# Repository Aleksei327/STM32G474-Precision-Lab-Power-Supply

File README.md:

# Precision Programmable Laboratory Power Supply

[Русская версия](README.ru.md)

A hardware development project for a galvanically isolated, fully programmable laboratory power supply. The design combines a tracking synchronous buck preregulator with a fast linear post-regulator to provide high efficiency without giving up low output noise.

> **Development status (17 November 2026): the power supply is running and working.** Both boards are assembled and powered up; the synchronous buck preregulator with its tracking loop, the linear post-regulator and the digital current limit all work under load. Verified on the bench so far: regulated output from near zero to 50 V into a resistive load, a 35-minute run at 50 V / 0.63 A with the output held within 49.998–50.001 V, and the current limit holding from 1 mA to 1.5 A. Testing and assembly are in progress: operation at several amps, short-circuit behaviour, and accuracy measurements against a reference meter are next. Until those results are published, the specification table below lists design targets. The KiCad sources here are still the August 2026 revision — fixes found during bring-up are not merged yet.

*The assembled boards on the bench: main board, auxiliary flyback board, and the display on the diagnostics page of the bring-up firmware (55 V input switched off for the photo).*

## Target specifications

| Parameter | Target / current design |
| --- | --- |
| Output voltage | 0–50 V programmable; expected practical lower limit approximately 20–50 mV |
| Voltage setting increment | approximately 0.84 mV; 1 mV user step |
| Current setting increment | 1 mA in firmware |
| Output ripple | no more than 1 mV target |
| Present transformer capability | approximately 5–6 A continuous, 8 A peak — the limiting element today |
| Pass-element thermal budget | 7 A continuous with the current heatsink and a silicone insulator; 10 A in short bursts under NTC foldback |
| Power-stage design target | up to 10 A after the transformer rewind (a mica insulator is then required on the pass FET) |
| Operating modes | CV, digital CC, programmable foldback, controlled output ramps |
| Controller | STM32G474 |
| Voltage reference and DAC | REF5025 + 16-bit DAC8830 |
| Voltage/current monitor | 20-bit INA228 with a Kelvin-connected 10 mΩ shunt |

## First measurements

Bring-up results from 9 November 2026, taken with bring-up firmware and before any calibration.

| Test | Result |
| --- | --- |
| Linear stage, 10.000 V setpoint into 1.5 kΩ | 10.088 V on the INA228, drift within ±2 mV over one minute; the +0.9 % offset is the uncalibrated reference |
| Zero setpoint | 0.003 V at the output |
| Buck stage, no load, 100 kHz, 55.6 V input | pass-FET drain voltage follows pulse length linearly from 12.5 V to 27.2 V |
| Buck switching node | clean rectangle, 58.8 V peak (about 3 V overshoot), no missed pulses |
| Buck no-load input power at 49 % pulse length | about 6.4 W, mostly inductor core loss — under investigation |

Since then (17 November 2026) the tracking loop, the current limit and output up to 50 V have been verified under load — see the status note above. Still ahead: load currents of several amps, short-circuit protection in operation, and calibrated accuracy measurements.

## The working device (November 2026)

Photos from the bench on 17 November 2026, English interface. The PC control program is available as a download — see [Firmware and PC program](#firmware-and-pc-program).

*The bench during testing: the main board (copper side up) with its auxiliary boards, the display and the oscilloscope.*

*The device display, Bench page: 12.000 V / 0.1501 A into a resistive load, buck at 150 kHz tracking the output.*

*PC control panel, Bench tab: setpoint, current limit and a live trace of output voltage and current.*

*Device screen tab: a live mirror of the instrument display, controlled from the PC.*

*Screen mock-up tab: the new main screen (CV/CC, OCP) running on live data.*

*Service tab: buck, auxiliary rails, INA228 metering and protection diagnostics.*

*Charts tab: output voltage, current and temperatures.*

*Sounds tab: the event sounds of the device.*

*48 V setpoint into an 80 Ω test load.*

*3.3 V setpoint into the same load.*

## Firmware and PC program

**Download: [Releases](https://github.com/Aleksei327/STM32G474-Precision-Lab-Power-Supply/releases)** — the PC program for Windows, Linux and macOS, the firmware update file (`.dpfw`, uploaded from the program over USB) and the full image for a first installation on a blank STM32G474. The source code is closed; binaries only.

| Without a key | With a key — **5 € per device** |
|---|---|
| Bench in the program: readings, setpoints, output on/off; current calibration; the device screen and settings; firmware updates; all protections | Engineering mode on the device; the engineering tabs of the program (service, charts, device screen, controls, sounds, console); the charger for Li-ion, Li-ion HV (4.35 V), LiFePO4, lead-acid and NiMH |

Locked tabs can be previewed in the program before buying. To get a key, click **Copy ID** in the program and write to the developer (see [Author](#author)). Payment is by cryptocurrency, bank transfer (IBAN) or card; you get the payment details first and the key once paid.

## Full schematic

The schematic is an A1 sheet. Open the SVG directly for lossless zoom.

[Russian schematic](docs/images/lab-psu-schematic-ru.svg)

## Boards

Two home-etched boards in one KiCad file: a single-sided main board of about 201 × 116 mm and an auxiliary flyback board of about 34 × 82 mm that generates the +67 V / −5 V rails for the post-regulator. The +12 V auxiliary supply comes from a separate small **55 → 12 V board** (UC3845 buck, its own KiCad project) — the on-board MP9486A stage of the first revision was removed.

**Single-sided:** the only etched copper is the bottom layer (B.Cu). The tracks drawn on F.Cu, In1.Cu and In2.Cu are **not copper layers** — they document the hand-wired wire jumpers and twisted pairs, layer by layer; everything on them is wired by hand.

*Copper side of the etched and assembled first-revision main board.*

[More views, layout details and the conventions used → PCB page](docs/pcb.md) · [55 → 12 V board](docs/power-55-12v.md)

## Reducing output noise — plans for the next revision

What the bring-up showed and what the next board revision will change to bring the output noise down further:

- **Re-arrange the DC-DC (buck) and the linear stage** so that the high-current switching loops are as short and as small as possible — smaller loops mean less ringing and less magnetic pick-up into the regulator and the measurement circuits.
- **Common-mode filter at the buck output** (in VDRAIN and its return) so that switching noise does not ride on the ground into the precision part.
- **Split the ground into two zones joined only through that filter:**
  - *buck ground* — from the 55 V input up to the switch driver (input capacitors, switches, driver, buck inductor and its capacitors);
  - *quiet ground* — everything after the switches: the controller and all its circuitry, the DAC and reference, INA228, the OPA454 linear stage and the shunt;
  - on the buck ground stay only the sensors of the primary voltages and the buck voltage, plus the fans and the relays.

## How it works

The mains front end is based on a modified 500 W ATX supply. Its active PFC stage creates an approximately 380 V DC bus, followed by a two-switch forward converter that provides galvanic isolation and an approximately 55 V secondary rail.

An STM32G474 controls a synchronous buck stage through HRTIM. The buck output tracks the requested output voltage while maintaining only about 2–2.5 V across the linear pass MOSFET. A damped C–L–C filter attenuates switching components before the OPA454-based linear post-regulator removes the remaining ripple.

A 16-bit DAC8830 and REF5025 establish the voltage setpoint. An INA228 measures terminal voltage and shunt current; firmware implements the programmable current limit and foldback characteristic. Fast short-circuit interception does not depend on that digital loop: the STM32 analog front end drives the hardware comparator and HRTIM break input, while firmware simultaneously clears the voltage DAC and opens the output relay.

The output stage also includes reverse-polarity detection, external-voltage detection before relay closure, overvoltage protection, backfeed supervision, a fuse, surge clamps, thermal monitoring, and an independent thermal relay interlock.

## Documentation

- [System architecture and protection design](docs/architecture.md)
- [Auxiliary +67 V / −5 V flyback converter](docs/auxiliary-flyback.md)
- [PCB design and boards](docs/pcb.md)
- [55 → 12 V auxiliary supply board](docs/power-55-12v.md)
- [Русская техническая документация](README.ru.md)

## Hardware sources

The complete KiCad 10 project is in [`hardware/`](hardware/README.md): schematic, layout, the project footprint library, hand-written 3D models with the Python scripts that generate them, and the SKiDL script the netlist is built from. The 55 → 12 V board is in [`hardware/55-12V/`](hardware/55-12V/).

⚠️ The boards are drawn for home etching: **every drill hole in the file is a 0.6 mm pilot** that is opened up by hand afterwards. Restore the real diameters before sending these files to a fab.

## License and reuse

The documentation, the schematic and the hardware design files are published under [CC BY-NC-ND 4.0](LICENSE): read them, study them, share them with attribution, but no commercial use and no publishing of modified versions. **Building a single unit for your own private use is explicitly permitted** — the exact terms are in [NOTICE.md](NOTICE.md).

**The firmware and PC program source code is closed.** Ready-to-use binaries are in [Releases](https://github.com/Aleksei327/STM32G474-Precision-Lab-Power-Supply/releases); the advanced functions are unlocked by a per-device key, see [Firmware and PC program](#firmware-and-pc-program).

## Author

Aleksei Subbotin — embedded electronics and power control, France / remote. Open to freelance and contract work: [github.com/Aleksei327](https://github.com/Aleksei327) · <alsubfr@hotmail.com>

## Safety

This project contains rectified mains and an approximately 380 V DC bus. It is an engineering prototype, not a certified product. Construction and testing require appropriate isolation, current limiting, discharge procedures, protective equipment, and experience with lethal-voltage power electronics.

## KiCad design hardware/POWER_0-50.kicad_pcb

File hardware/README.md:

# Hardware sources

[Русская версия](README.ru.md) · [Back to the project overview](../README.md)

KiCad 10 project for the 0–50 V precision laboratory power supply. Open `POWER_0-50.kicad_pro`; the project-local footprint library resolves through `${KIPRJMOD}`, so no global library setup is needed.

> **Work in progress, published as-is.** The first revision has been built and is working; this is revision v0.2.61 with the bring-up fixes merged, not yet fabricated. Expect to find mistakes, and read [`docs/pcb.md`](../docs/pcb.md) before reusing anything — in particular the 0.6 mm pilot-hole convention, which will ruin a fab order if left as it is.

## Files

| Path | What it is |
| --- | --- |
| `POWER_0-50.kicad_sch` | schematic, single sheet (A1) |
| `POWER_0-50.kicad_pcb` | layout: 2 boards, 235 footprints, single-sided main board (B.Cu); F.Cu / In1.Cu / In2.Cu show hand-wired jumpers and twisted pairs, not copper (revision v0.2.61) |
| `Library.pretty/` | 28 project footprints (see below) |
| `Library.3dshapes/` | 17 hand-written 3D models plus the Python generators that produce them |
| `netlist/lab_psu_skidl.py` | SKiDL script that generates the netlist — the electrical source of truth |
| `netlist/lab_psu.net` | generated netlist, the reference the schematic and the PCB are checked against |
| `netlist/lab_psu_chips.kicad_sym` | symbols for the parts KiCad does not ship |
| `55-12V/` | separate KiCad project of the 55 → 12 V auxiliary supply board with its footprints and 3D models — see [docs/power-55-12v.md](../docs/power-55-12v.md) |

## Project footprint library

Everything that is either not in the stock libraries or had to be adapted for hand assembly:

- **Modules:** WeAct STM32G474CEU6 core board, Adafruit-style INA228 breakout (its screw terminal shares pad numbers with the header pins, so a wire can be soldered to whichever is convenient).
- **HSOP-8 with exposed pad, hand-solder pads:** `UCC27211` (EP → GND), `OPA454` (**EP → V− = −5 V**, not ground — see the datasheet).
- **Mechanical parts as real footprints:** three heatsinks, the constantan shunt staple, the flyback transformer on its measured bobbin, relays, the wound toroids, a THT NTC.
- Wide-pad SOIC-8/16 variants and various through-hole passives for parts that dissipate more than an SMD package can take.

## 3D models

KiCad 10 ships only STEP models, and several stock footprints in this project reference STEP files that are not in the distribution at all. The missing parts were modelled by hand as VRML and are generated by the scripts in `Library.3dshapes/_generators/`:

```
python wrlgen.py    # primitives, heatsinks, wound toroids, relays
python wrlgen2.py   # module boards, flyback transformer, NTC, SMD inductor
python wrlgen3.py   # fuse holder, connectors, shunt staple
python stand.py R21,J6   # preview rig: copies the board, keeps only the named parts
```

Two things worth knowing if you edit them: one VRML unit is 2.54 mm, the model Y axis is the negative of the board Y axis, and **KiCad's VRML loader does not draw the built-in `Cylinder` primitive at all** — every round shape here is an explicit `IndexedFaceSet` mesh.

## Netlist generator

The schematic was not drawn by hand first: `netlist/lab_psu_skidl.py` builds the circuit in SKiDL, and the resulting netlist is the reference that both the schematic and the board are verified against. If you change the circuit there, note that new parts must be appended at the **end** of the script — inserting them in the middle renumbers every later reference designator and silently desynchronises the board.

## Firmware

Not included. The firmware is not published yet, and this hardware does not operate without it — see [NOTICE.md](../NOTICE.md).

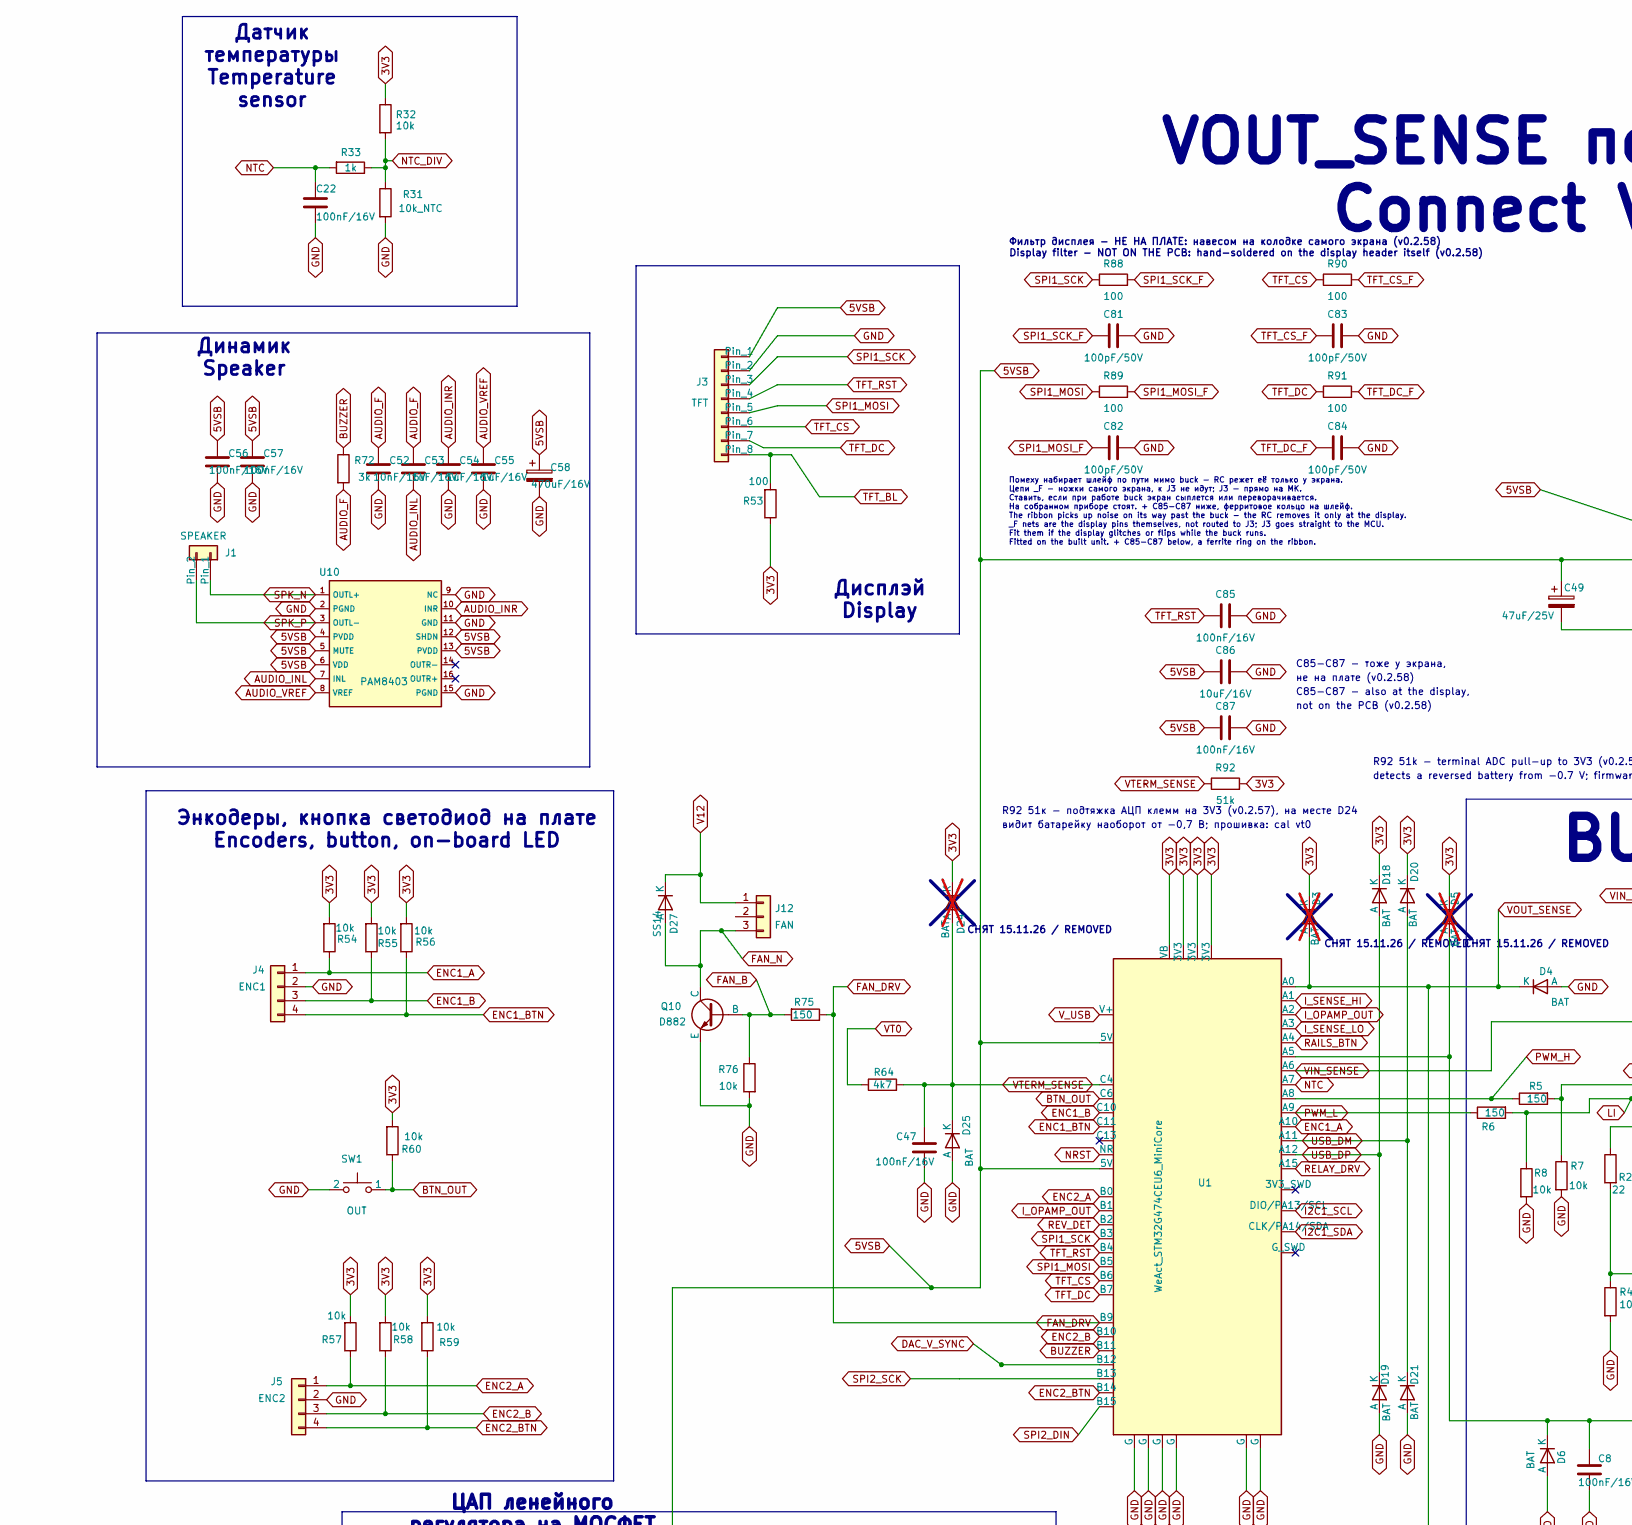
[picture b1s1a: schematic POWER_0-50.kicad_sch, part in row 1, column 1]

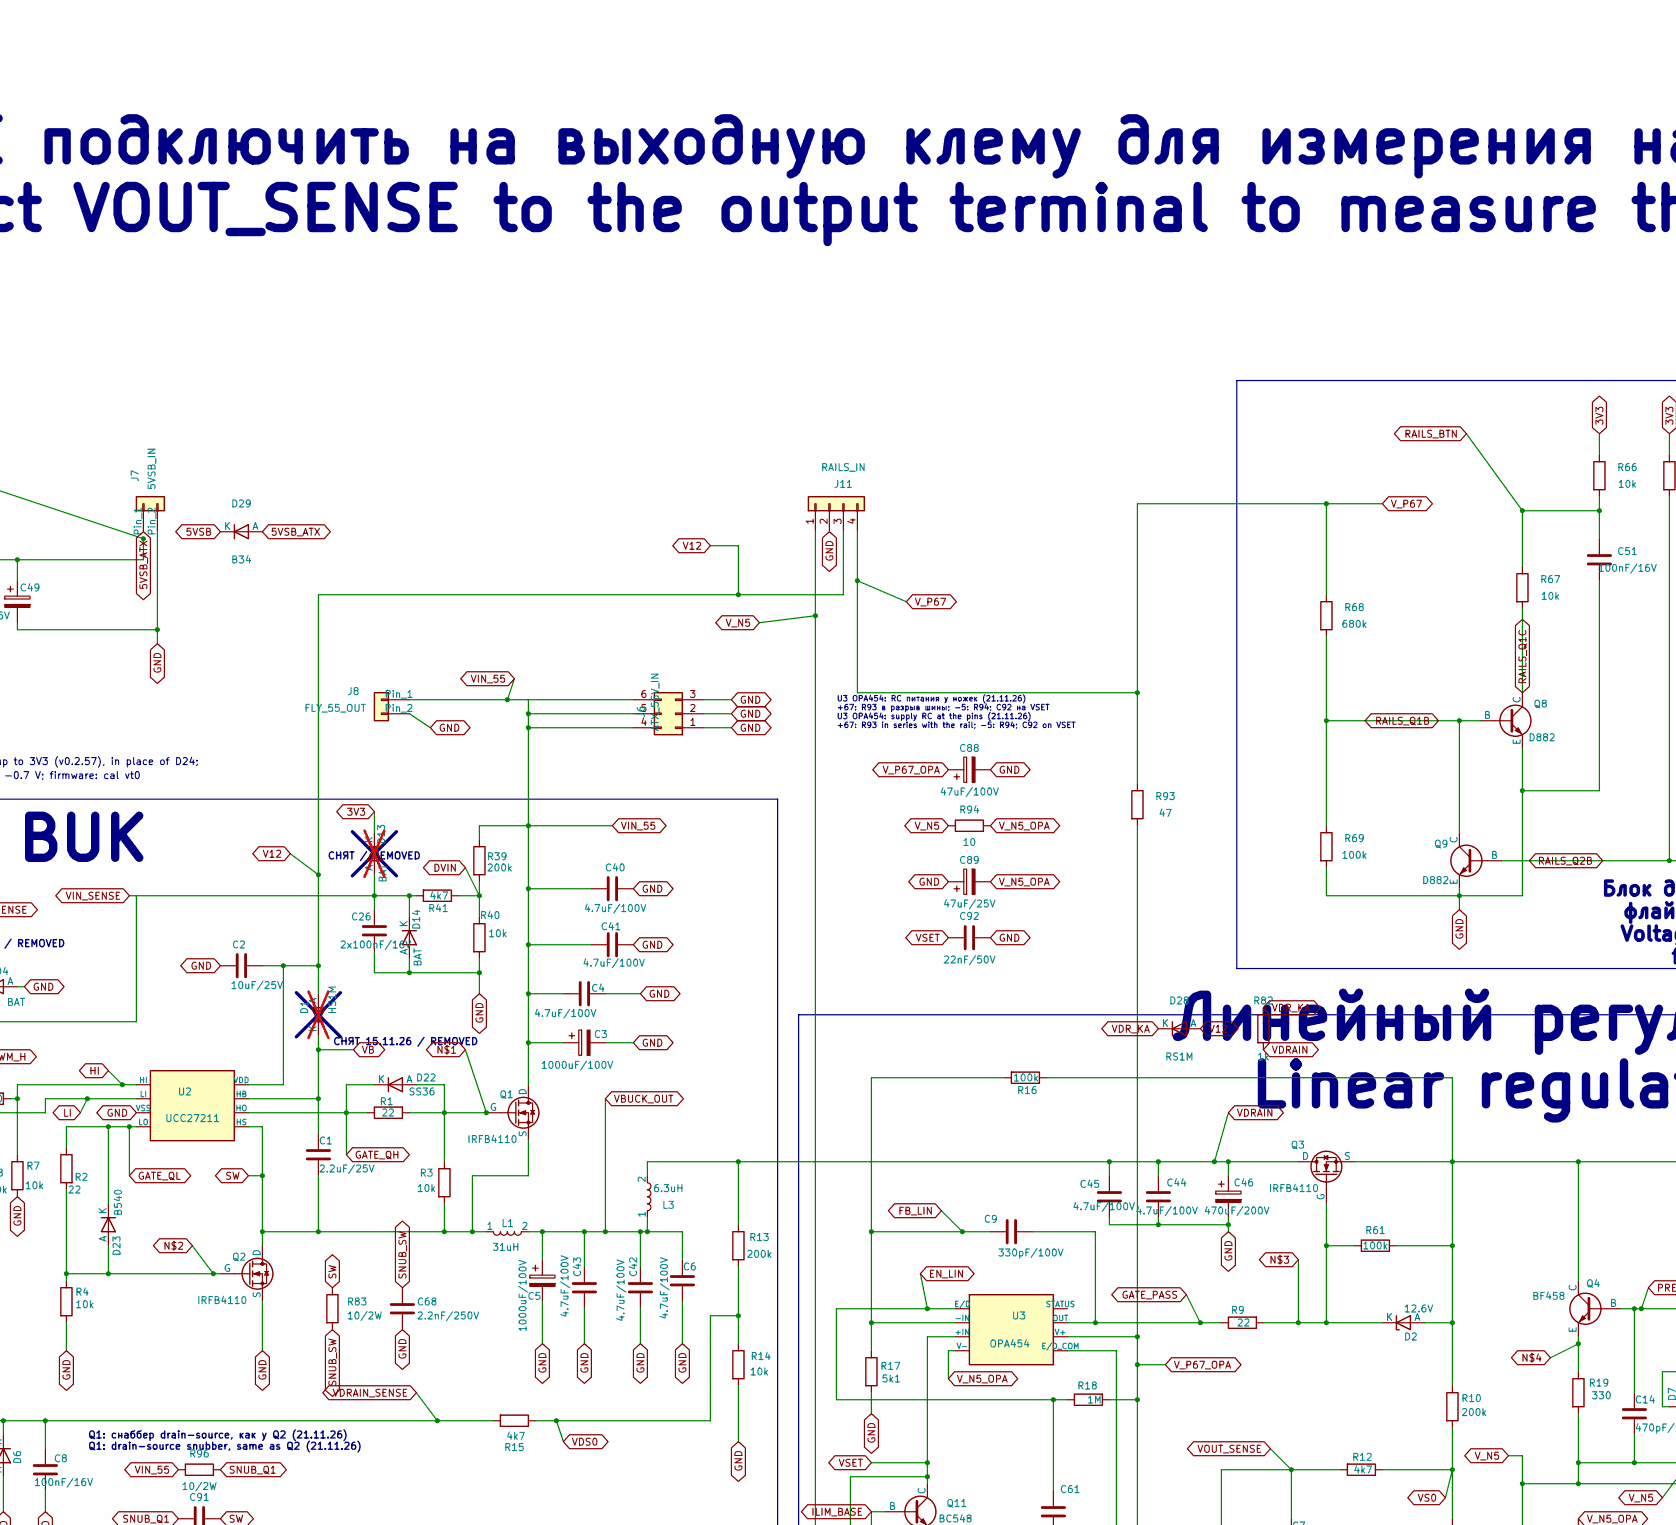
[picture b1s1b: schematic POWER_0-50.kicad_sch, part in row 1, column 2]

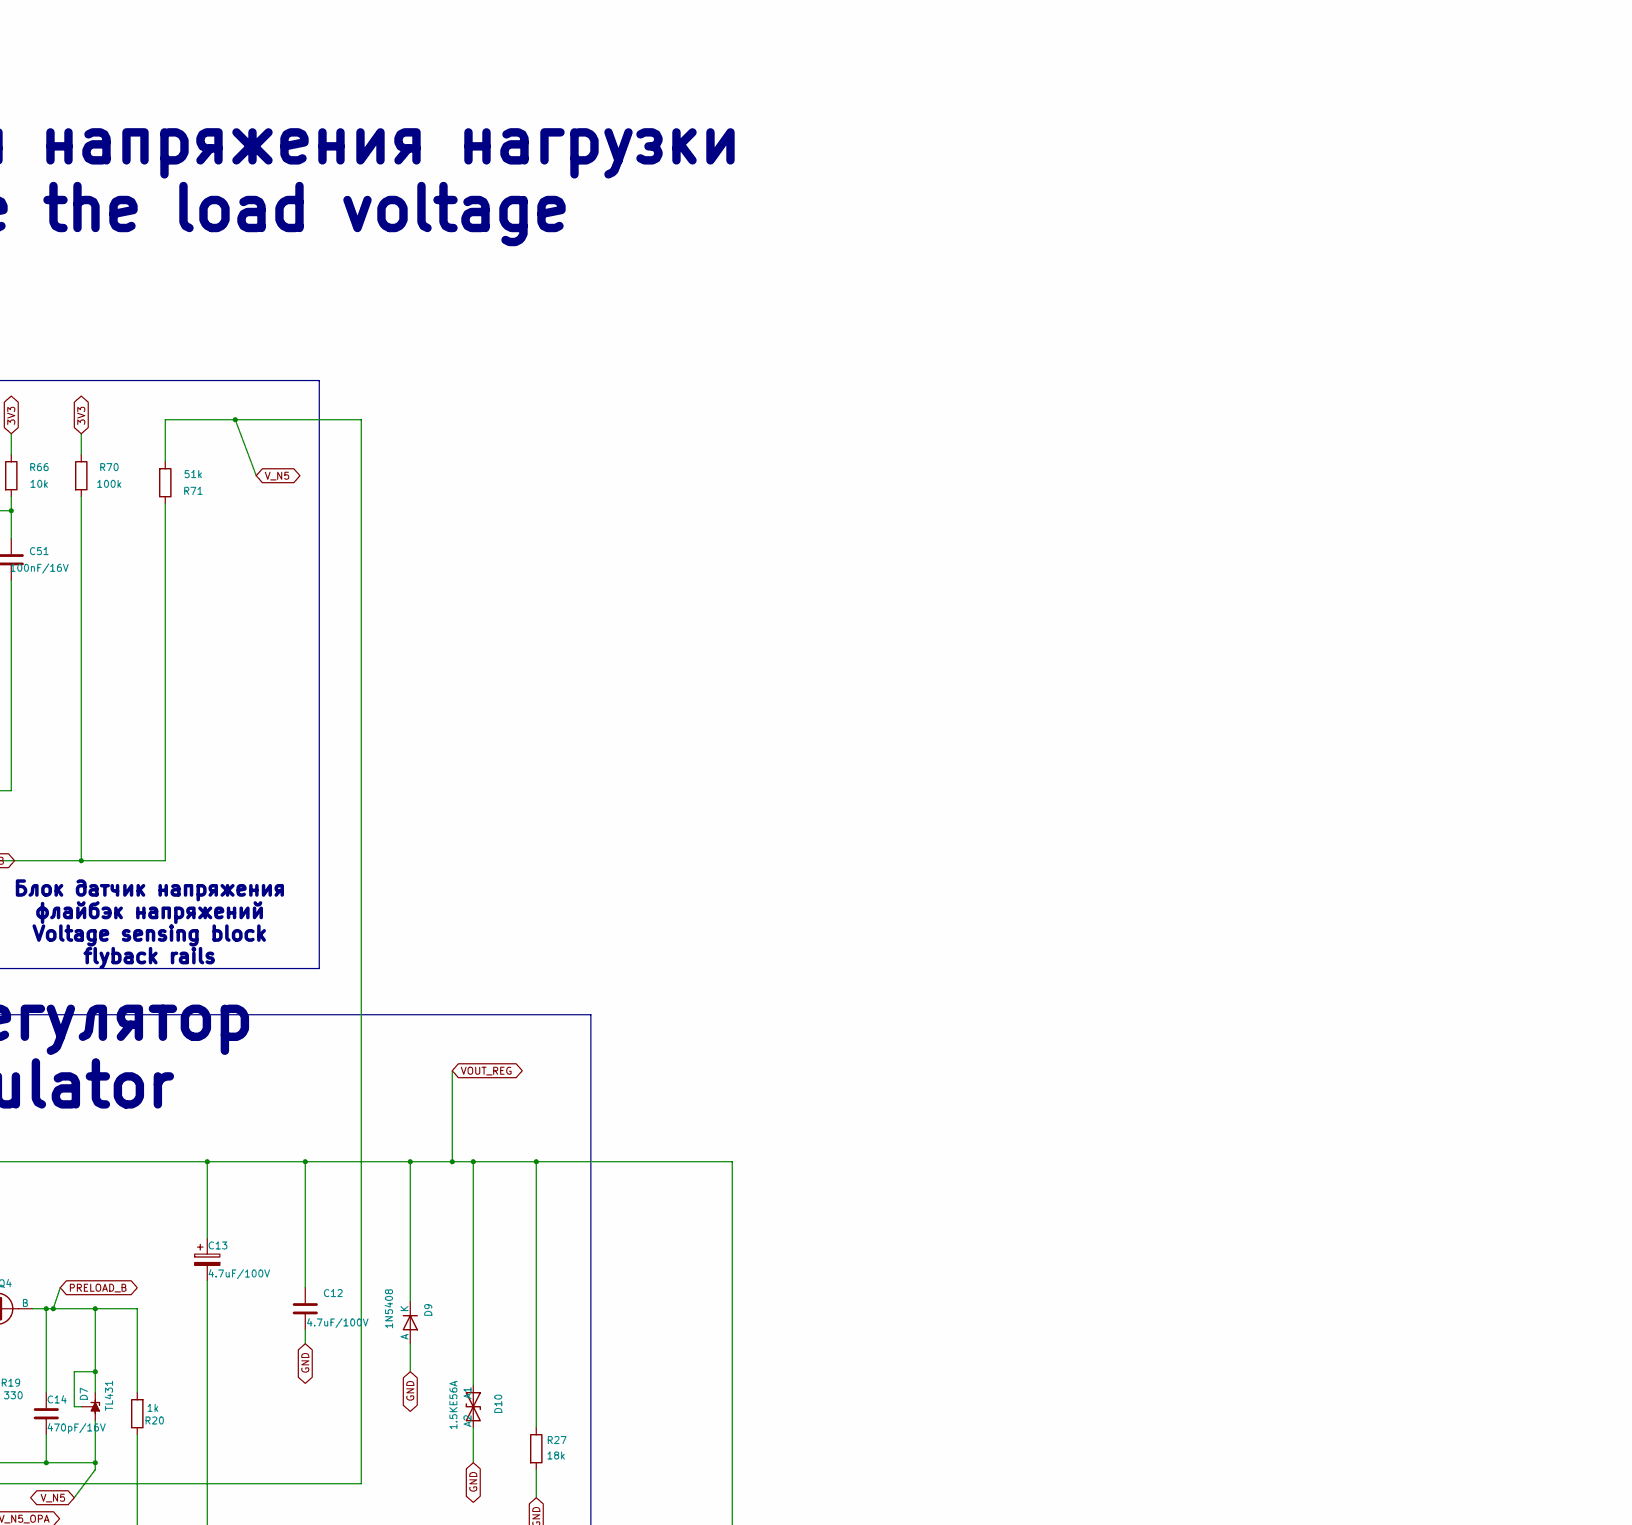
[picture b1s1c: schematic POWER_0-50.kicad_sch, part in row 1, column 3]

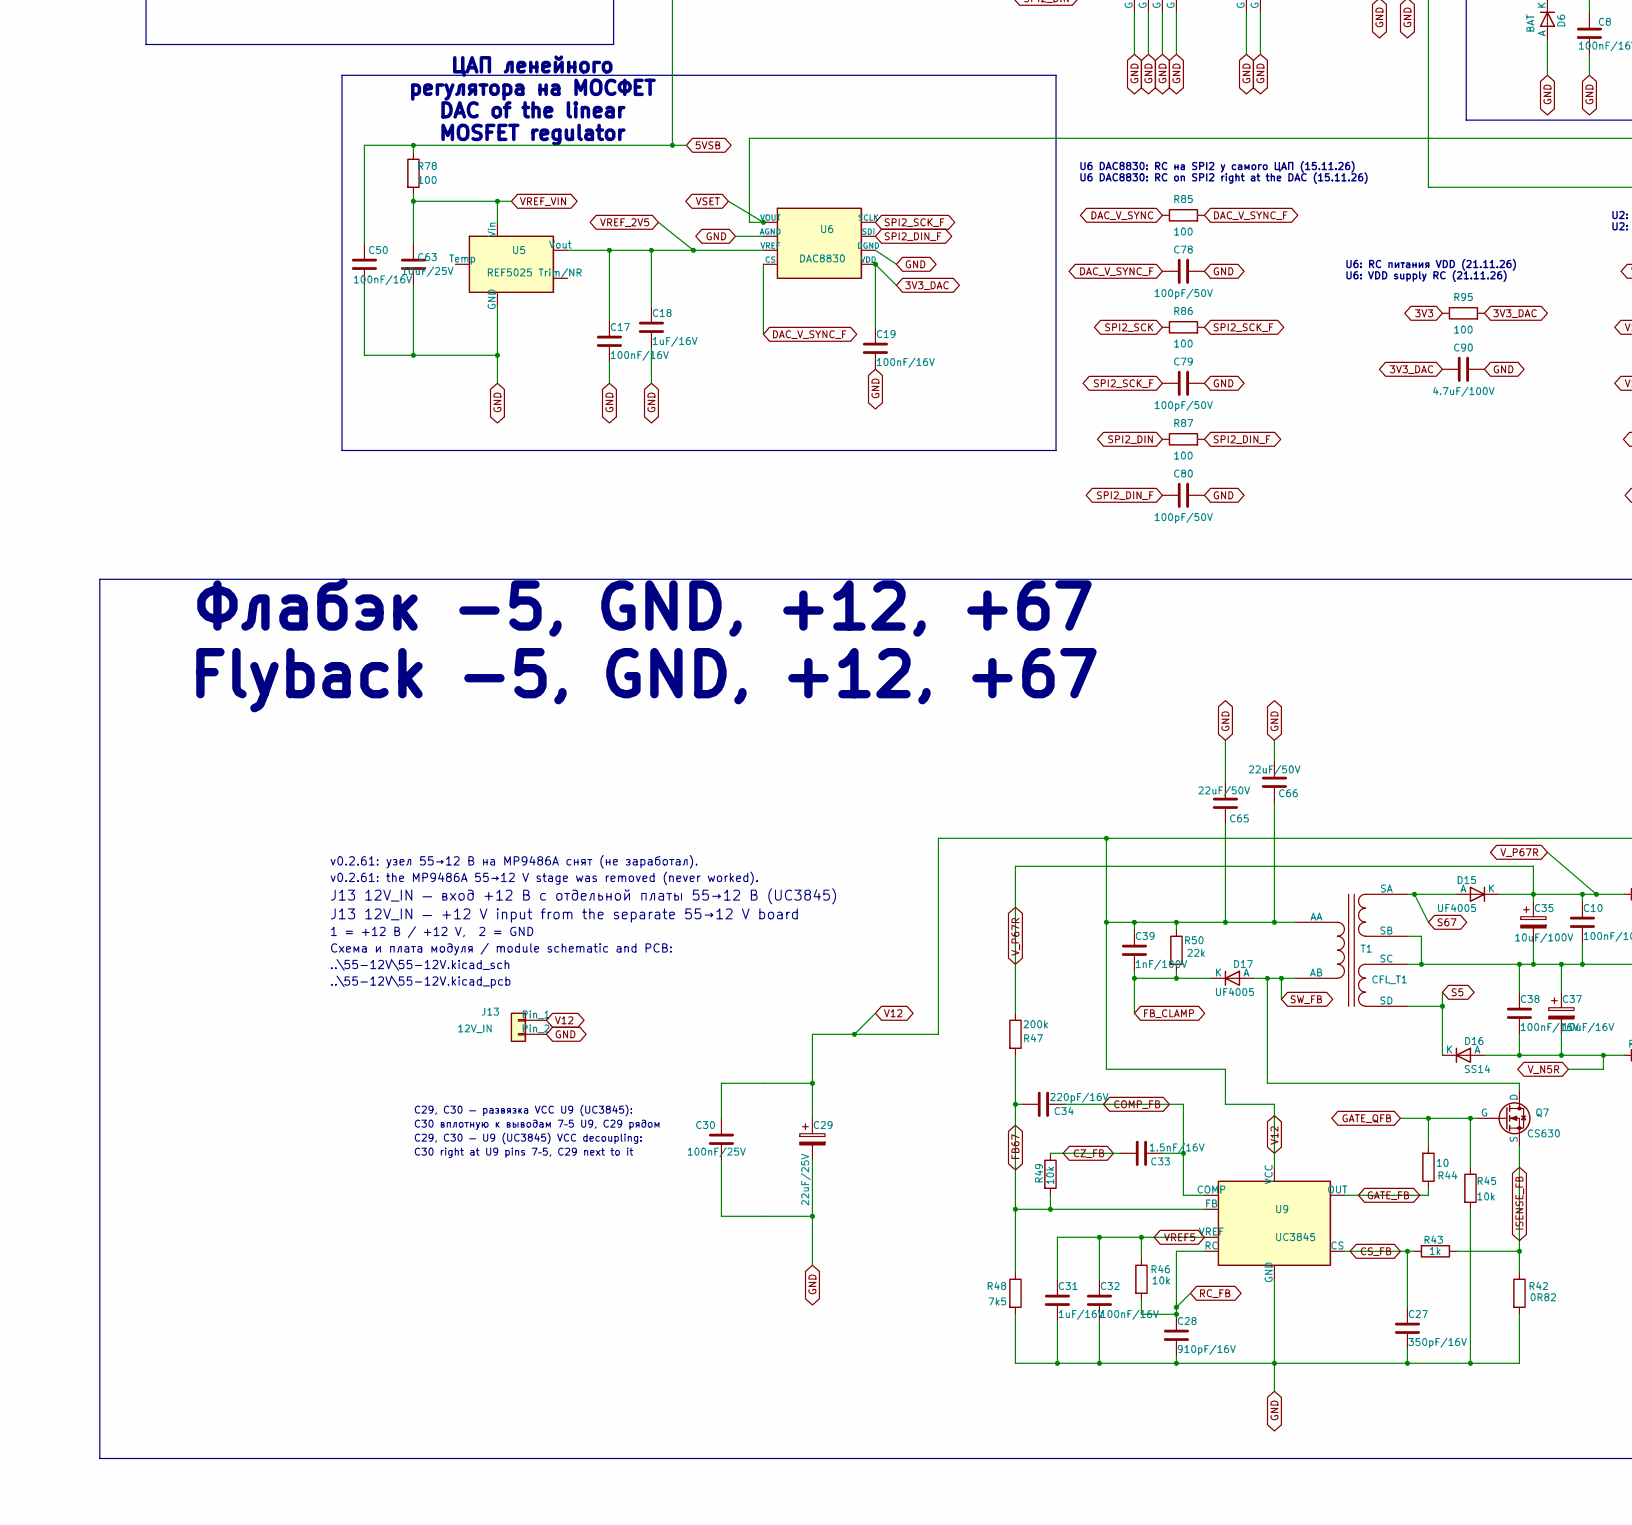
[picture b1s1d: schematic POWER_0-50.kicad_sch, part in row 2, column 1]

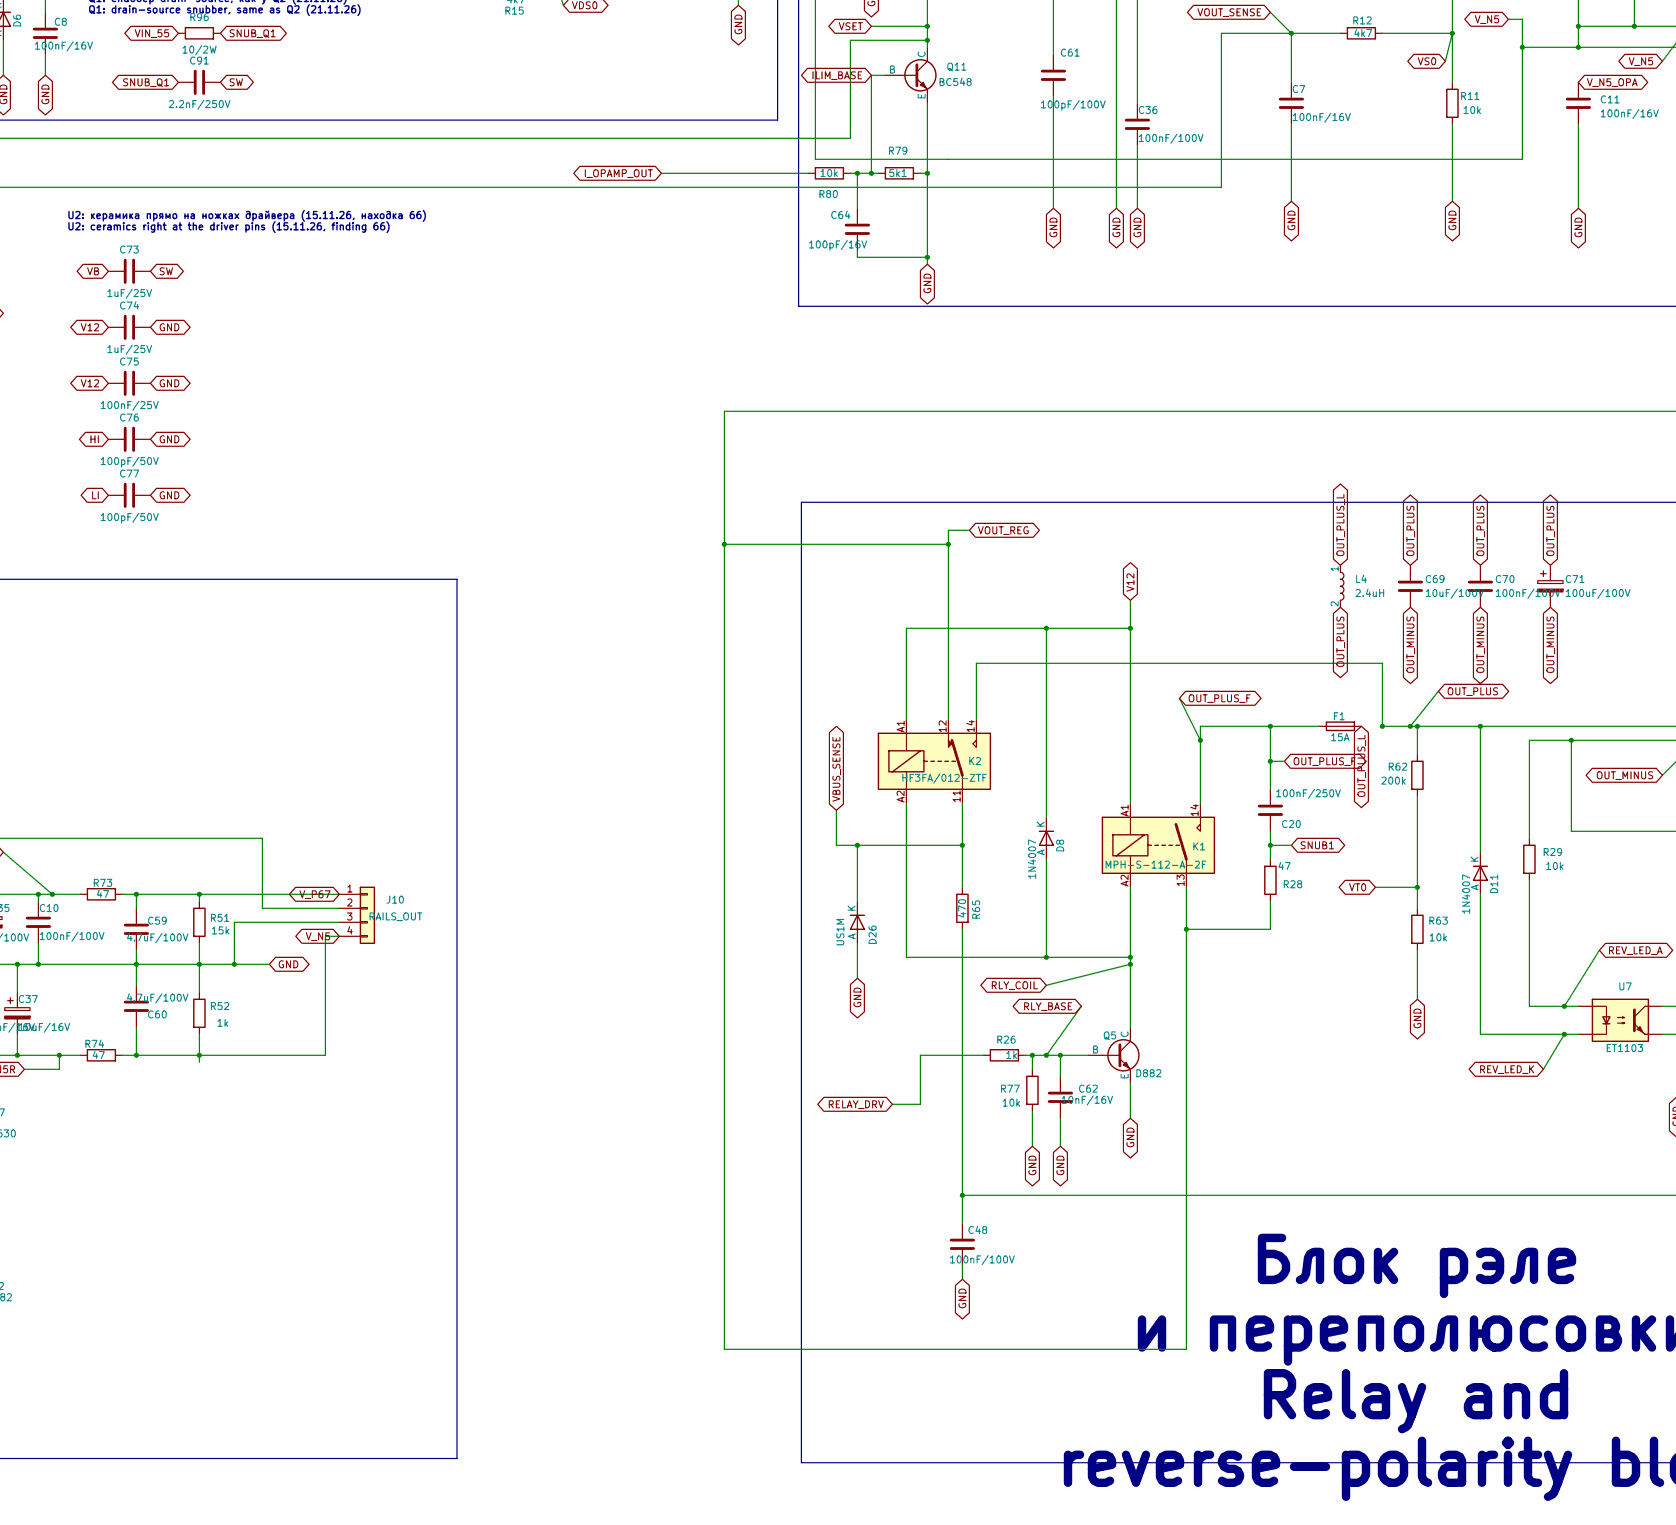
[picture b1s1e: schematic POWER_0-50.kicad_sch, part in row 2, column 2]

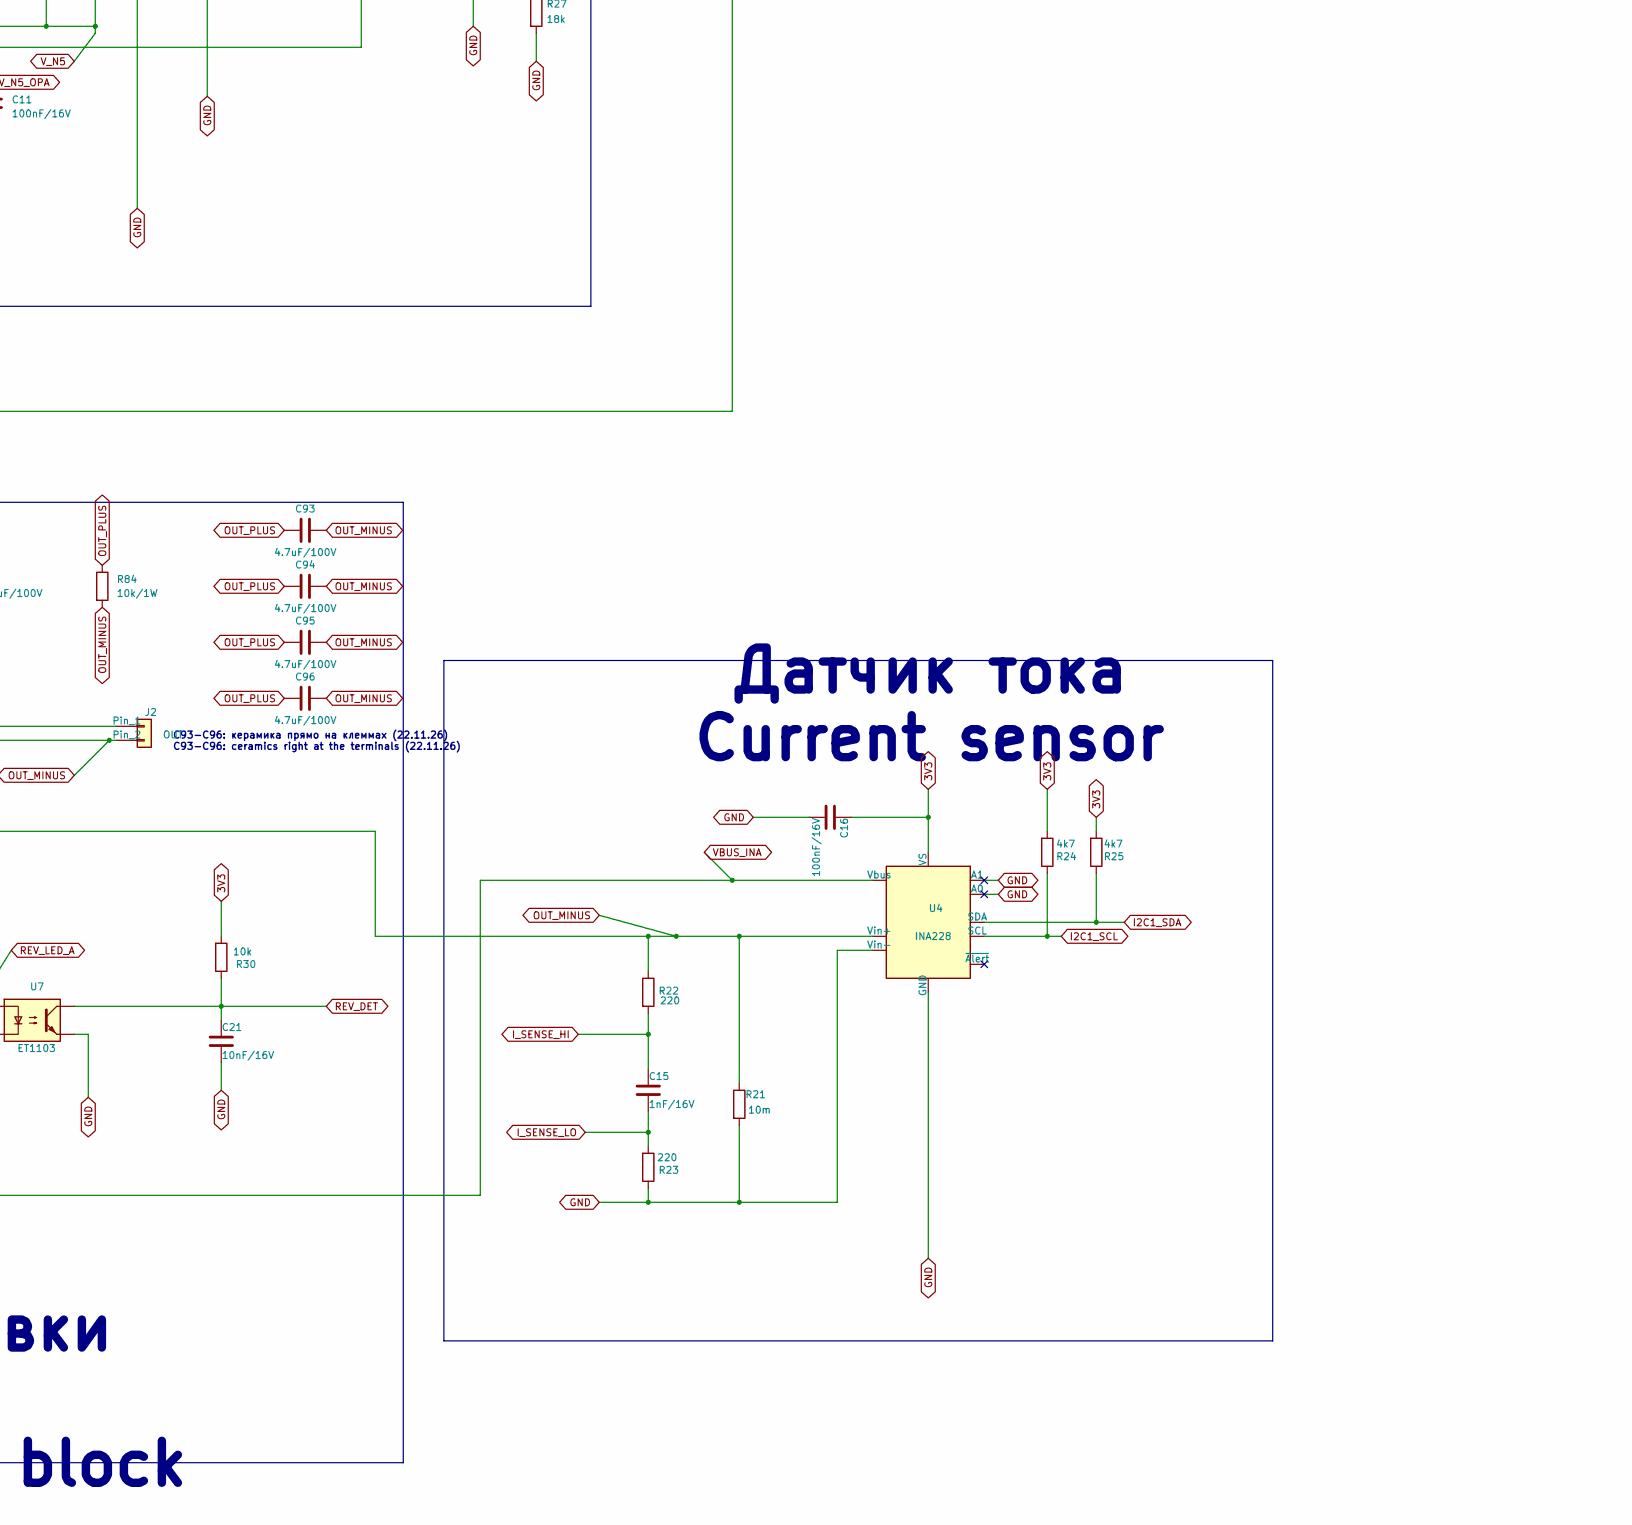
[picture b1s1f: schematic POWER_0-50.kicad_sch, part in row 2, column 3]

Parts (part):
C1: 2.2uF/25V; C_1206_3216Metric
C2, C63: 10uF/25V; C_1206_3216Metric
C3, C5: 1000uF/100V; CP_Radial_D18.0mm_P7.50mm
C4, C6, C12, C13, C40, C41, C42, C43, C44, C45, C59, C60, C90, C93, C94, C95, C96: 4.7uF/100V; C_1206_3216Metric
C7, C8, C11, C16, C17, C19, C22, C32, C38, C47, C50, C51, C56, C57, C85, C87: 100nF/16V; C_1206_3216Metric
C9: 330pF/100V; C_1206_3216Metric
C10, C36, C48, C70: 100nF/100V; C_1206_3216Metric
C14: 470pF/16V; C_1206_3216Metric
C15: 1nF/16V; C_1206_3216Metric
C18, C31, C53, C54, C55: 1uF/16V; C_1206_3216Metric
C20: 100nF/250V; C_1206_3216Metric
C21, C52, C62: 10nF/16V; C_1206_3216Metric
C26: 2x100nF/16V; C_1206_3216Metric
C27: 350pF/16V; C_1206_3216Metric
C28: 910pF/16V; C_1206_3216Metric
C29: 22uF/25V; CP_Radial_D10.0mm_P5.00mm
C30, C75: 100nF/25V; C_1206_3216Metric
C33: 1.5nF/16V; C_1206_3216Metric
C34: 220pF/16V; C_1206_3216Metric
C35: 10uF/100V; CP_Radial_D10.0mm_P5.00mm
C37: 10uF/16V; CP_Radial_D10.0mm_P5.00mm
C39: 1nF/100V; C_1206_3216Metric
C46: 470uF/200V; CP_Radial_D13.0mm_P5.00mm
C49: 47uF/25V; CP_Radial_D10.0mm_P5.00mm
C58: 470uF/16V; CP_Radial_D10.0mm_P5.00mm
C61: 100pF/100V; C_1206_3216Metric
C64: 100pF/16V; C_1206_3216Metric
C65, C66: 22uF/50V; C_1210_3225Metric
C68, C91: 2.2nF/250V; C_Disc_D7.5mm_W5.0mm_P5.00mm
C69: 10uF/100V; C_1210_3225Metric
C71: 100uF/100V; CP_Radial_D10.0mm_P5.00mm
C73, C74: 1uF/25V; C_1206_3216Metric
C76, C77, C78, C79, C80, C81, C82, C83, C84: 100pF/50V; C_1206_3216Metric
C86: 10uF/16V; C_1206_3216Metric
C88: 47uF/100V; CP_Radial_D10.0mm_P5.00mm
C89: 47uF/25V; CP_Radial_D6.3mm_P2.50mm
C92: 22nF/50V; C_1206_3216Metric
D1: HS1M; D_SMA; not fitted
D2: 12.6V; D_DO-35_SOD27_P10.16mm_Horizontal
D3, D5, D13, D24: BAT; D_SOD-323_HandSolder; not fitted
D4, D6, D14, D18, D19, D20, D21, D25: BAT; D_SOD-323_HandSolder
D7: TL431; TO-126-3_Vertical_TO92body
D8: 1N4007; D_DO-201AD_P15.24mm_Horizontal
D9: 1N5408; D_DO-201AD_P15.24mm_Horizontal
D10: 1.5KE56A; D_DO-201AD_P15.24mm_Horizontal
D11: 1N4007; D_DO-35_SOD27_P10.16mm_Horizontal
D15, D17: UF4005; D_DO-41_SOD81_P10.16mm_Horizontal
D16, D27: SS14; D_SMA
D22: SS36; D_SMC
D23: B540; D_SMC
D26: US1M; D_SMC
D28: RS1M; D_SMA
D29: B34; D_SMA
F1: 15A; Fuseholder_Clip-5x20mm_Littelfuse_100_Inline_P20.50x4.60mm_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
J1: SPEAKER; Conn_JST_XH_1x02_D0.6
J2: OUT; TerminalBlock_MaiXu_MX126-5.0-02P_1x02_P5.00mm
J3: TFT; PinHeader_1x08_P2.54mm_Vertical
J4: ENC1; JST_EH_B4B-EH-A_1x04_P2.50mm_Vertical
J5: ENC2; JST_EH_B4B-EH-A_1x04_P2.50mm_Vertical
J6: ATX_55V_IN; Conn_PWR55_MiniFit_2x03_D0.6
J7: 5VSB_IN; Conn_JST_XH_1x02_D0.6
J8: FLY_55_OUT; Conn_FLY55_JST_EH_1x03_P2.5_pins13
J10: RAILS_OUT; Conn_RAILS_1x04_P2.54_D0.6
J11: RAILS_IN; PinSocket_1x04_P2.54mm_Vertical
J12: FAN; Conn_FAN_JST_PH_1x03_pins13
J13: 12V_IN; Conn_JST_XH_1x02_D0.6
K1: MPH-S-112-A-2F; Relay_MPH_1A
K2: HF3FA/012-ZTF; Relay_HF3FA_1C
L1: 31uH; L_Toroid_Vertical_Core25x10mm_P14.00mm_D1.8mm
L3: 6.3uH; L_Toroid_Vertical_Core21x7mm_P10.00mm_D2.0mm
L4: 2.4uH; L_Toroid_Vertical_Core21x7mm_P10.00mm_D2.0mm
Q1, Q2, Q3: IRFB4110; TO-220-3_Vertical
Q4: BF458; TO-126-3_Vertical
Q5, Q8, Q9, Q10: D882; TO-126-3_Vertical
Q7: CS630; TO-252-2
Q11: BC548; TO-92_in_TO-126_pads_CBE
R1, R2: 22; R_2512_6332Metric
R3, R4, R7, R8, R11, R14, R30, R32, R40, R45, R46, R49, R54, R55, R56, R57, R58, R59, R60, R63, R66, R67, R76, R77: 10k; R_1206_3216Metric
R5, R6, R75: 150; R_1206_3216Metric
R9: 22; R_Axial_DIN0207_L6.3mm_D2.5mm_P10.16mm_Horizontal
R10, R13, R39, R47, R62: 200k; R_1206_3216Metric
R12, R15, R24, R25, R41, R64: 4k7; R_1206_3216Metric
R16: 100k; R_0805_2012Metric
R17: 5k1; R_0805_2012Metric
R18: 1M; R_1206_3216Metric
R19: 330; R_1206_3216Metric
R20, R26, R33, R43, R52, R82: 1k; R_1206_3216Metric
R21: 10m; Shunt_Constantan_Staple_P20mm
R22, R23: 220; R_1206_3216Metric
R27: 18k; R_Axial_DIN0207_L6.3mm_D2.5mm_P10.16mm_Horizontal
R28: 47; R_Axial_DIN0207_L6.3mm_D2.5mm_P10.16mm_Horizontal
R29: 10k; R_Axial_DIN0207_L6.3mm_D2.5mm_P10.16mm_Horizontal
R31: 10k_NTC; NTC_THT_P7.00mm_Pad2.0mm_D0.6mm
R42: 0R82; R_Axial_DIN0411_L9.9mm_D3.6mm_P12.70mm_Horizontal
R44, R94: 10; R_1206_3216Metric
R48: 7k5; R_1206_3216Metric
R50: 22k; R_1206_3216Metric
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
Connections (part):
3V3: C16.1, D3.1 (K), D5.1 (K), D13.1 (K), D18.1 (K), D20.1 (K), D24.1 (K), R24.2, R25.2, R30.2, R32.1, R53.1, R54.2, R55.2, R56.2, R57.2, R58.2, R59.2, R60.2, R66.1, R70.1, R92.2, R95.1, U1.3 (3V3), U1.4 (3V3), U1.22 (VB), U1.23 (3V3), U4.6 (VS)
3V3_DAC: C19.1, C90.1, R95.2, U6.8 (VDD)
5VSB: C49.1, C50.1, C56.1, C57.1, C58.1, C86.1, C87.1, D29.1 (K), J3.1, R78.1, U1.27 (5V), U1.28 (5V), U10.4 (PVDD), U10.5 (MUTE), U10.6 (VDD), U10.12 (SHDN), U10.13 (PVDD)
5VSB_ATX: D29.2 (A), J7.1
AUDIO_F: C52.1, C53.1, R72.2
AUDIO_INL: C53.2, U10.7 (INL)
AUDIO_INR: C54.1, U10.10 (INR)
AUDIO_VREF: C55.1, U10.8 (VREF)
BTN_OUT: R60.1, SW1.1, U1.33 (C6)
BUZZER: R72.1, U1.5 (B11)
COMP_FB: C33.1, C34.1, U9.1 (COMP)
CS_FB: C27.1, R43.2, U9.3 (CS)
CZ_FB: C33.2, R49.1
DAC_V_SYNC: R85.1, U1.29 (B12)
DAC_V_SYNC_F: C78.1, R85.2, U6.4 (CS)
DVIN: R39.2, R40.1, R41.1
ENC1_A: J4.1, R54.1, U1.36 (A10)
ENC1_B: J4.3, R55.1, U1.40 (C10)
ENC1_BTN: J4.4, R56.1, U1.41 (C11)
ENC2_A: J5.1, R57.1, U1.10 (B0)
ENC2_B: J5.3, R58.1, U1.6 (B10)
ENC2_BTN: J5.4, R59.1, U1.31 (B14)
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
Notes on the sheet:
VOUT_SENSE подключить на выходную клему для измерения напряжения нагрузки Connect VOUT_SENSE to the output terminal to measure the load voltage
Динамик Speaker
Флабэк -5, GND, +12, +67 Flyback -5, GND, +12, +67
Блок датчик напряжения флайбэк напряжений Voltage sensing block flyback rails
Датчик температуры Temperature sensor
Дисплэй Display
Линейный регулятор Linear regulator
ЦАП ленейного регулятора на МОСФЕТ DAC of the linear MOSFET regulator
Блок рэле и переполюсовки Relay and reverse-polarity block
Датчик тока Current sensor
BUK
Энкодеры, кнопка светодиод на плате Encoders, button, on-board LED
СНЯТ 15.11.26 / REMOVED
СНЯТ / REMOVED
U2: керамика прямо на ножках драйвера (15.11.26, находка 66) U2: ceramics right at the driver pins (15.11.26, finding 66)
U6 DAC8830: RC на SPI2 у самого ЦАП (15.11.26) U6 DAC8830: RC on SPI2 right at the DAC (15.11.26)
Фильтр дисплея - НЕ НА ПЛАТЕ: навесом на колодке самого экрана (v0.2.58) Display filter - NOT ON THE PCB: hand-soldered on the display header itself (v0.2.58)
R92 51к - подтяжка АЦП клемм на 3V3 (v0.2.57), на месте D24
видит батарейку наоборот от -0,7 В; прошивка: cal vt0
C85-C87 - тоже у экрана,
не на плате (v0.2.58)
U6: RC питания VDD (21.11.26) U6: VDD supply RC (21.11.26)
Q1: снаббер drain-source, как у Q2 (21.11.26) Q1: drain-source snubber, same as Q2 (21.11.26)
C93-C96: керамика прямо на клеммах (22.11.26) C93-C96: ceramics right at the terminals (22.11.26)
v0.2.61: узел 55→12 В на MP9486A снят (не заработал).
v0.2.61: the MP9486A 55→12 V stage was removed (never worked).
J13 12V_IN — вход +12 В с отдельной платы 55→12 В (UC3845)
J13 12V_IN — +12 V input from the separate 55→12 V board
1 = +12 В / +12 V, 2 = GND
Схема и плата модуля / module schematic and PCB:
..\55-12V\55-12V.kicad_sch
..\55-12V\55-12V.kicad_pcb
C85-C87 - also at the display,
not on the PCB (v0.2.58)
Помеху набирает шлейф по пути мимо buck - RC режет её только у экрана. Цепи _F - ножки самого экрана, к J3 не идут; J3 - прямо на МК. Ставить, если при работе buck экран сыплется или переворачивается. На собранном приборе стоят. + C85-C87 ниже, ферритовое кольцо на шлейф. The ribbon picks up noise 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
R92 51k - terminal ADC pull-up to 3V3 (v0.2.57), in place of D24;
detects a reversed battery from -0.7 V; firmware: cal vt0
U3 OPA454: RC питания у ножек (21.11.26) +67: R93 в разрыв шины; -5: R94; C92 на VSET U3 OPA454: supply RC at the pins (21.11.26) +67: R93 in series with the rail; -5: R94; C92 on VSET
C29, C30 — развязка VCC U9 (UC3845):
C30 вплотную к выводам 7–5 U9, C29 рядом
